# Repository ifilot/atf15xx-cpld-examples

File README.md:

# ATF15XX CPLD Examples

## Purpose

This repository contains a number of examples how to design and program for the
[ATF15XX](https://ww1.microchip.com/downloads/en/DeviceDoc/Atmel-3614-CPLD-ATF15-Overview.pdf)
range of CPLDs.

## Devices

Unless otherwise stated, we make use the [ATF15XX-DK3 development programmer
kit](https://www.microchip.com/en-us/development-tool/atf15xx-dk3-u).

## Programming instructions

Program instructions are provided in the design file, but a brief overview
is also presented here.

* Download and install WinCUPL and ATMISP via 
  [this link](https://www.microchip.com/en-us/products/fpgas-and-plds/spld-cplds/pld-design-resources)
* Open the `.pld` file in WinCUPL
* Do `Run > Device Dependent Compile` or simply hit `F9`: This will generate a
  `.jed` file.
* Open the ATMISP tool and select `File > New`. Number of devices is `1`.
* Select ATF1504AS (or your specific device) for the *Device Name*, select
  `Program / Verify` under *JTAG Instruction* and select the JEDEC file as
  generated in the previous step.
* Click `Run` to place the design on the CPLD. Note that the ATF1502 chip
  needs to have its own 5V power supply. The ATDH1150USB is (apparently)
  unable to provide power to the chip over the JTAG port.

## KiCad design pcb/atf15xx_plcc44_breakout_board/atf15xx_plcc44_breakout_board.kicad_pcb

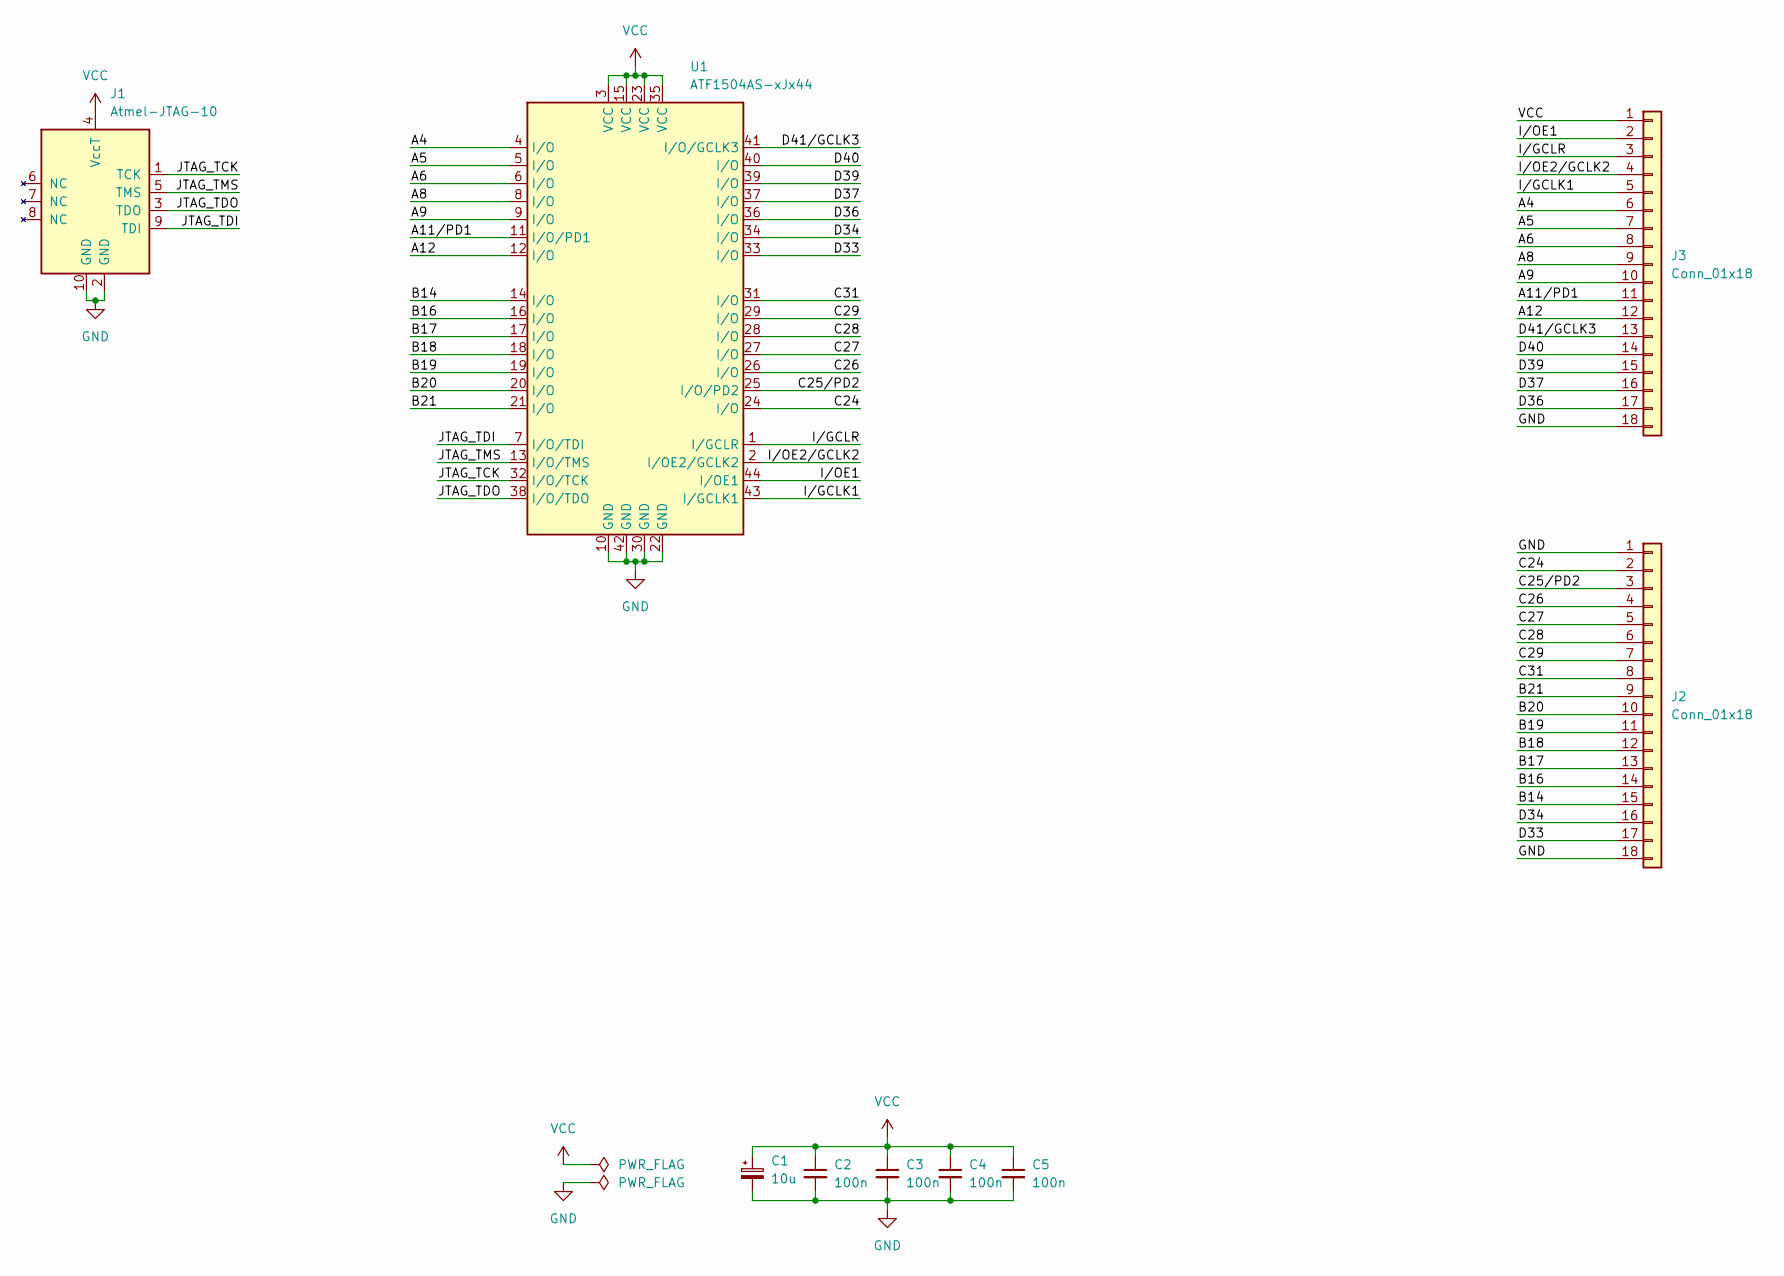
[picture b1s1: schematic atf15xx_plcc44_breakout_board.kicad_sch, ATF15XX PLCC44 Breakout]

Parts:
C1: 10u; CP_Radial_D4.0mm_P1.50mm
C2, C3, C4, C5: 100n; C_0805_2012Metric_Pad1.18x1.45mm_HandSolder
J1: Atmel-JTAG-10; IDC-Header_2x05_P2.54mm_Vertical
J2, J3: Conn_01x18; PinHeader_1x18_P2.54mm_Vertical
U1: ATF1504AS-xJx44; PLCC-44_THT-Socket

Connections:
/A4: J3.6, U1.4 (I/O)
/A5: J3.7, U1.5 (I/O)
/A6: J3.8, U1.6 (I/O)
/A8: J3.9, U1.8 (I/O)
/A9: J3.10, U1.9 (I/O)
/A11/PD1: J3.11, U1.11 (I/O/PD1)
/A12: J3.12, U1.12 (I/O)
/B14: J2.15, U1.14 (I/O)
/B16: J2.14, U1.16 (I/O)
/B17: J2.13, U1.17 (I/O)
/B18: J2.12, U1.18 (I/O)
/B19: J2.11, U1.19 (I/O)
/B20: J2.10, U1.20 (I/O)
/B21: J2.9, U1.21 (I/O)
/C24: J2.2, U1.24 (I/O)
/C25/PD2: J2.3, U1.25 (I/O/PD2)
/C26: J2.4, U1.26 (I/O)
/C27: J2.5, U1.27 (I/O)
/C28: J2.6, U1.28 (I/O)
/C29: J2.7, U1.29 (I/O)
/C31: J2.8, U1.31 (I/O)
/D33: J2.17, U1.33 (I/O)
/D34: J2.16, U1.34 (I/O)
/D36: J3.17, U1.36 (I/O)
/D37: J3.16, U1.37 (I/O)
/D39: J3.15, U1.39 (I/O)
/D40: J3.14, U1.40 (I/O)
/D41/GCLK3: J3.13, U1.41 (I/O/GCLK3)
/I/GCLK1: J3.5, U1.43 (I/GCLK1)
/I/GCLR: J3.3, U1.1 (I/GCLR)
/I/OE1: J3.2, U1.44 (I/OE1)
/I/OE2/GCLK2: J3.4, U1.2 (I/OE2/GCLK2)
/JTAG_TCK: J1.1 (TCK), U1.32 (I/O/TCK)
/JTAG_TDI: J1.9 (TDI), U1.7 (I/O/TDI)
/JTAG_TDO: J1.3 (TDO), U1.38 (I/O/TDO)
/JTAG_TMS: J1.5 (TMS), U1.13 (I/O/TMS)
GND: C1.2, C2.2, C3.2, C4.2, C5.2, J1.2 (GND), J1.10 (GND), J2.1, J2.18, J3.18, U1.10 (GND), U1.22 (GND), U1.30 (GND), U1.42 (GND)
VCC: C1.1, C2.1, C3.1, C4.1, C5.1, J1.4 (VccT), J3.1, U1.3 (VCC), U1.15 (VCC), U1.23 (VCC), U1.35 (VCC)

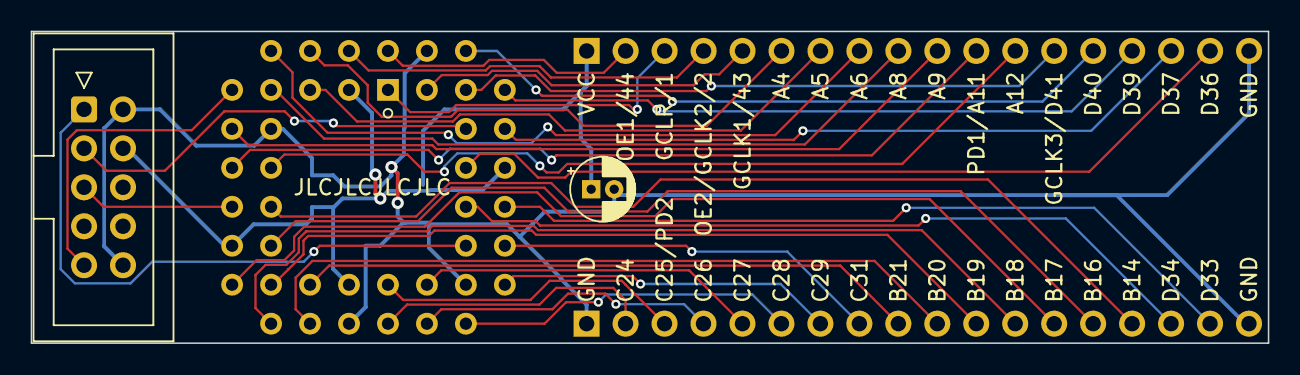
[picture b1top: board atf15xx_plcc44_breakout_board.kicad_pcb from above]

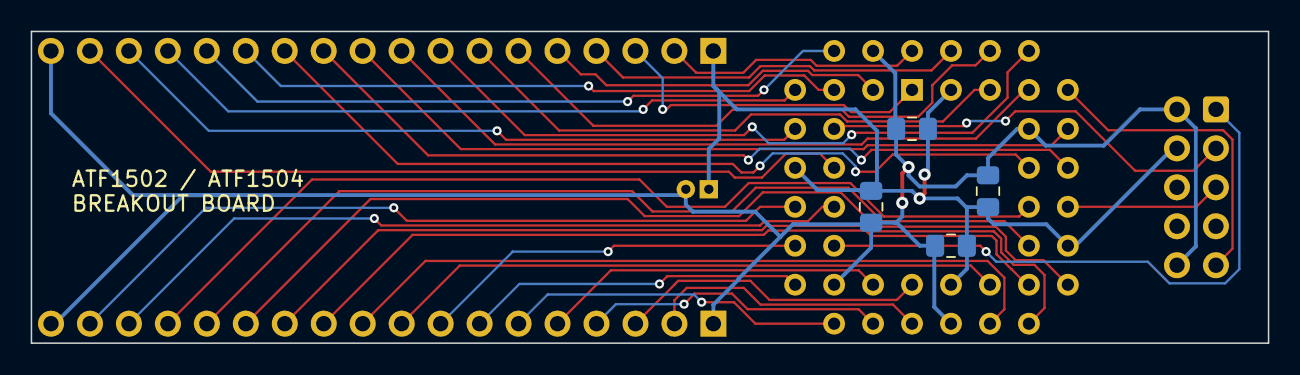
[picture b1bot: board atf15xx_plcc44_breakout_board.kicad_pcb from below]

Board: 2 copper layers, 80.6 x 20.3 mm, 9 parts (6 on the bottom side), 38 nets.

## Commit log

2025-03-22 Rewriting example for ATF1502 and adding breakout board
2025-03-22 Creating logics for joystick cartridge

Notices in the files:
pcb/atf15xx_plcc44_breakout_board/atf15xx_plcc44_breakout_board.kicad_pcb:
Licensed under CERN-OHL-W v2
Copyright © Adrien Kohlbecker
